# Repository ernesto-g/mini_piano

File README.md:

# Mini piano

Characteristics:

  - six-note keyboard
  - D major pentatonic scale
  - 12V power input

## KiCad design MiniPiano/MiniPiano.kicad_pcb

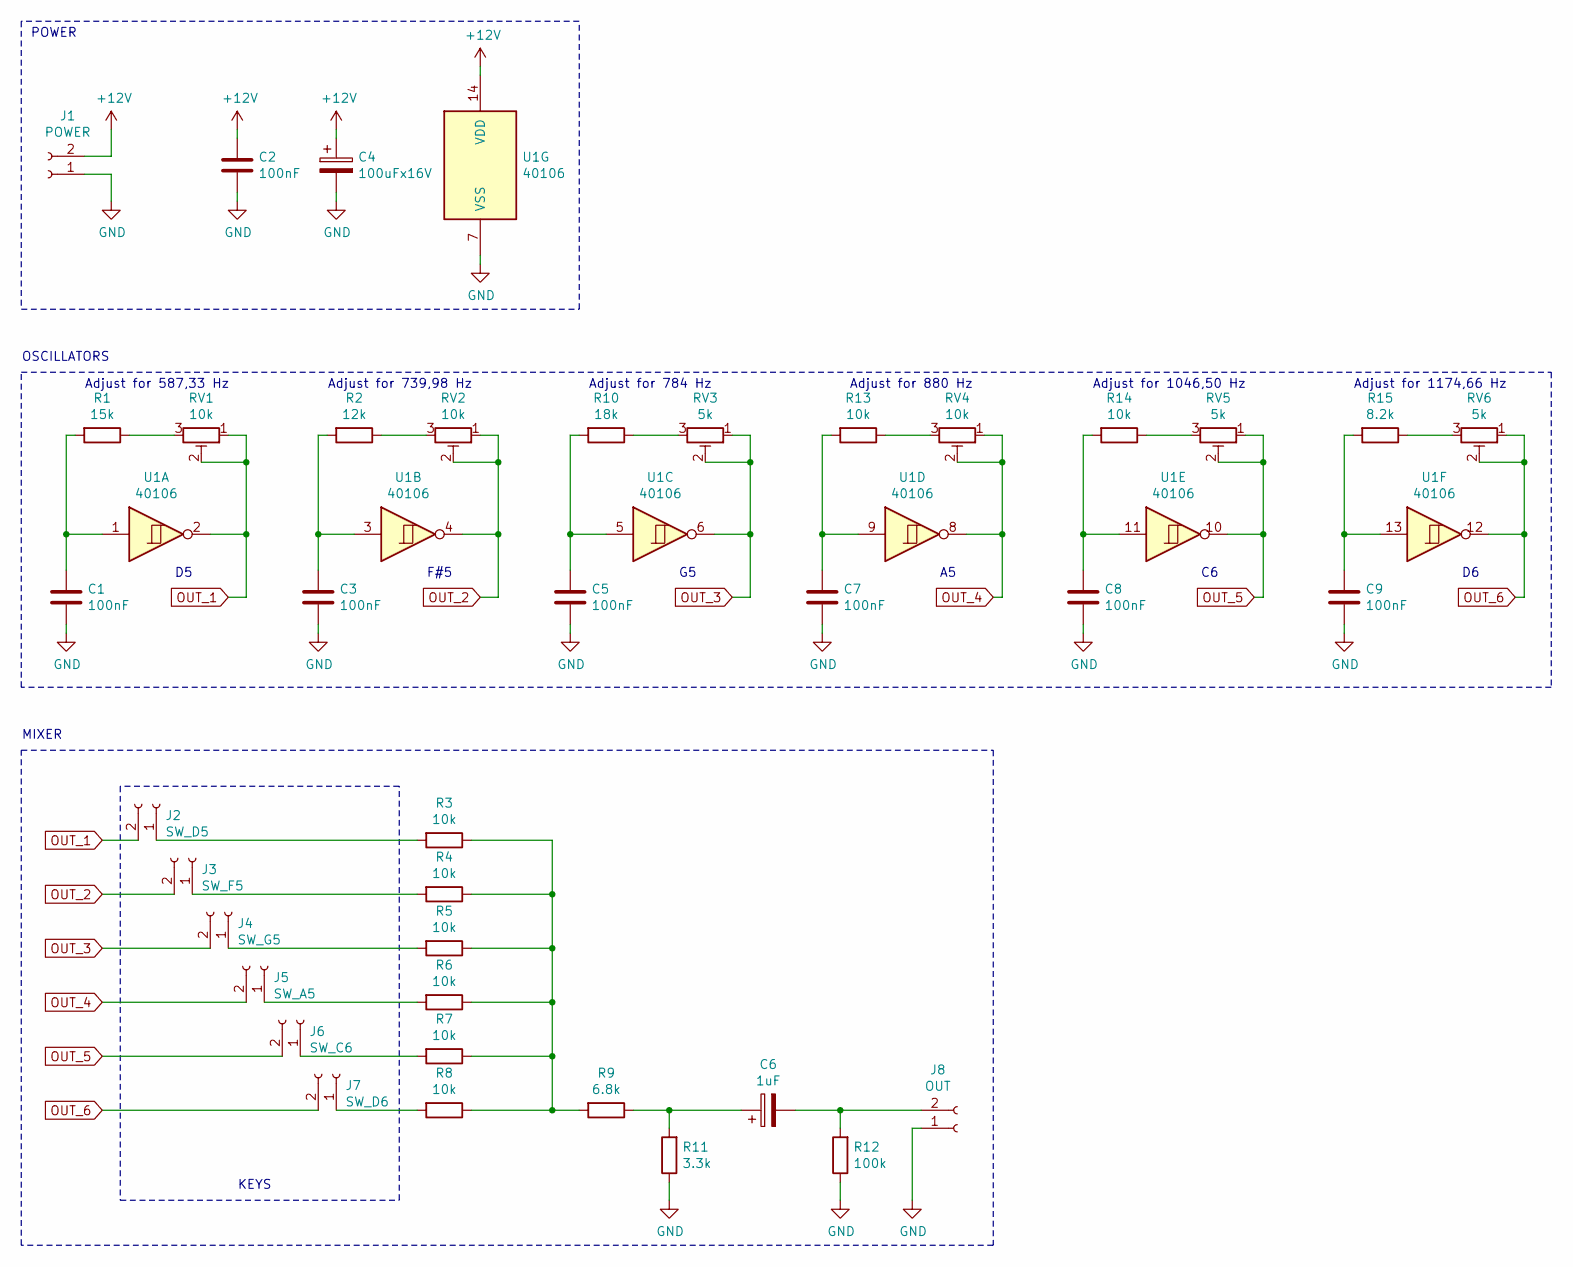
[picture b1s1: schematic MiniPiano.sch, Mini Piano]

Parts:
C1, C2, C3, C5, C7, C8, C9: 100nF; C_Disc_D4.7mm_W2.5mm_P5.00mm
C4: 100uFx16V; CP_Radial_D8.0mm_P3.50mm
C6: 1uF; CP_Radial_D8.0mm_P3.50mm
J1: POWER; PhoenixContact_MCV_1,5_2-G-3.81_1x02_P3.81mm_Vertical
J2: SW_D5; PhoenixContact_MCV_1,5_2-G-3.81_1x02_P3.81mm_Vertical
J3: SW_F5; PhoenixContact_MCV_1,5_2-G-3.81_1x02_P3.81mm_Vertical
J4: SW_G5; PhoenixContact_MCV_1,5_2-G-3.81_1x02_P3.81mm_Vertical
J5: SW_A5; PhoenixContact_MCV_1,5_2-G-3.81_1x02_P3.81mm_Vertical
J6: SW_C6; PhoenixContact_MCV_1,5_2-G-3.81_1x02_P3.81mm_Vertical
J7: SW_D6; PhoenixContact_MCV_1,5_2-G-3.81_1x02_P3.81mm_Vertical
J8: OUT; PhoenixContact_MCV_1,5_2-G-3.81_1x02_P3.81mm_Vertical
R1: 15k; R_Axial_DIN0204_L3.6mm_D1.6mm_P7.62mm_Horizontal
R2: 12k; R_Axial_DIN0204_L3.6mm_D1.6mm_P7.62mm_Horizontal
R3, R4, R5, R6, R7, R8, R13, R14: 10k; R_Axial_DIN0204_L3.6mm_D1.6mm_P7.62mm_Horizontal
R9: 6.8k; R_Axial_DIN0204_L3.6mm_D1.6mm_P7.62mm_Horizontal
R10: 18k; R_Axial_DIN0204_L3.6mm_D1.6mm_P7.62mm_Horizontal
R11: 3.3k; R_Axial_DIN0204_L3.6mm_D1.6mm_P7.62mm_Horizontal
R12: 100k; R_Axial_DIN0204_L3.6mm_D1.6mm_P7.62mm_Horizontal
R15: 8.2k; R_Axial_DIN0204_L3.6mm_D1.6mm_P7.62mm_Horizontal
RV1, RV2, RV4: 10k; Potentiometer_Piher_PT-6-V_Vertical
RV3, RV5, RV6: 5k; Potentiometer_Piher_PT-6-V_Vertical
U1: 40106; DIP-14_W7.62mm_LongPads

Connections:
+12V: C2.1, C4.1, J1.2, U1.14 (VDD)
GND: C1.2, C2.2, C3.2, C4.2, C5.2, C7.2, C8.2, C9.2, J1.1, J8.1, R11.1, R12.1, U1.7 (VSS)
unnamed: C1.1, R1.2, U1.1
unnamed: C3.1, R2.2, U1.3
unnamed: C5.1, R10.2, U1.5
unnamed: C6.1, R9.1, R11.2
unnamed: C6.2, J8.2, R12.2
unnamed: C7.1, R13.2, U1.9
unnamed: C8.1, R14.2, U1.11
unnamed: C9.1, R15.2, U1.13
unnamed: J2.1, R3.2
unnamed: J3.1, R4.2
unnamed: J4.1, R5.2
unnamed: J5.1, R6.2
unnamed: J6.1, R7.2
unnamed: J7.1, R8.2
unnamed: R1.1, RV1.3
unnamed: R2.1, RV2.3
unnamed: R3.1, R4.1, R5.1, R6.1, R7.1, R8.1, R9.2
unnamed: R10.1, RV3.3
unnamed: R13.1, RV4.3
unnamed: R14.1, RV5.3
unnamed: R15.1, RV6.3
OUT_1: J2.2, RV1.1, RV1.2, U1.2
OUT_2: J3.2, RV2.1, RV2.2, U1.4
OUT_3: J4.2, RV3.1, RV3.2, U1.6
OUT_4: J5.2, RV4.1, RV4.2, U1.8
OUT_5: J6.2, RV5.1, RV5.2, U1.10
OUT_6: J7.2, RV6.1, RV6.2, U1.12

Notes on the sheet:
POWER
OSCILLATORS
F#5
MIXER
KEYS
Adjust for 587,33 Hz
Adjust for 739,98 Hz
Adjust for 784 Hz
Adjust for 880 Hz
Adjust for 1046,50 Hz
Adjust for 1174,66 Hz

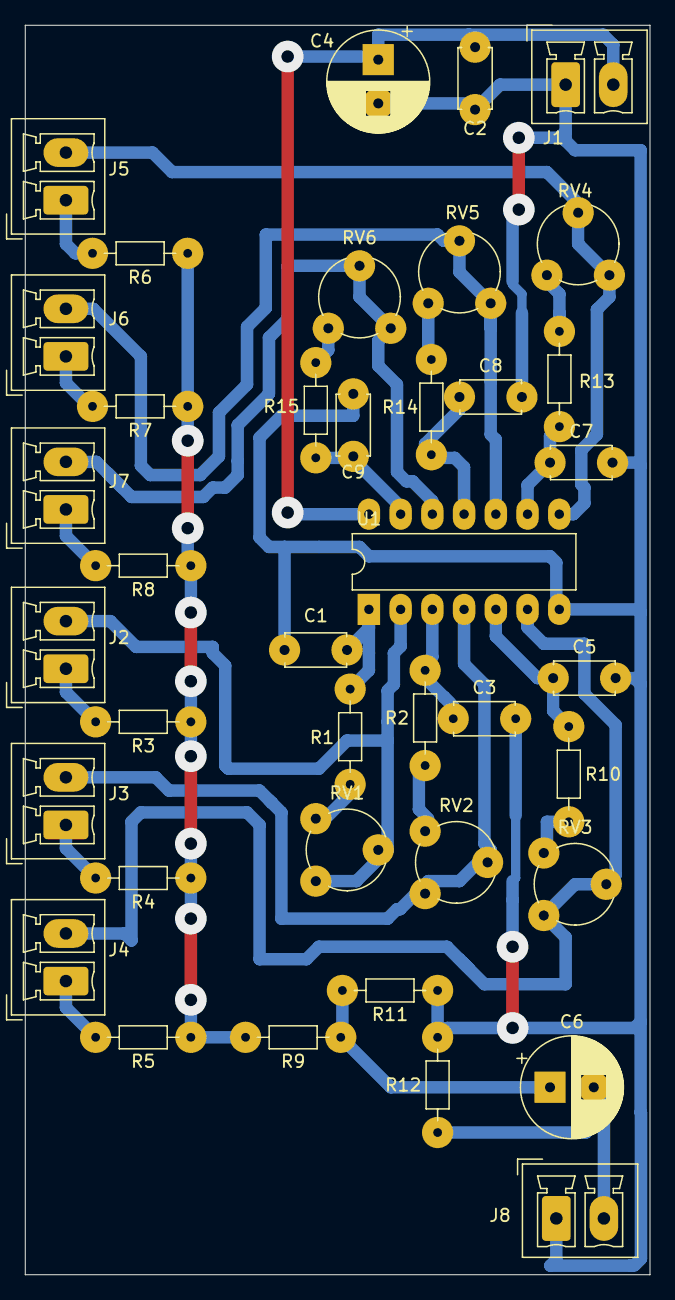
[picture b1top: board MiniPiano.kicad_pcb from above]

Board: 2 copper layers, 50.0 x 100.0 mm, 39 parts (0 on the bottom side), 29 nets.

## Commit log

2021-01-11 pictures
2022-01-09 fix valores de resistencias
2022-01-09 fix resistencias
